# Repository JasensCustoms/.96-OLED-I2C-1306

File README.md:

# .96-OLED-I2C-1306
JasensCustoms.com version of an I2C OLED Screen.

These are provided for personal use only under the CC BY-NC 4.0 (https://creativecommons.org/licenses/by-nc/4.0/). This is a place that basic PCB outlines, cable pinouts, etc. will reside. You are free to update and fix errors, provide more context, and cotnribute to the repo.

Mechanical Drawing:

As you can see, placement is very specific and accurate. Standard PCB thickness, 1.6mm.

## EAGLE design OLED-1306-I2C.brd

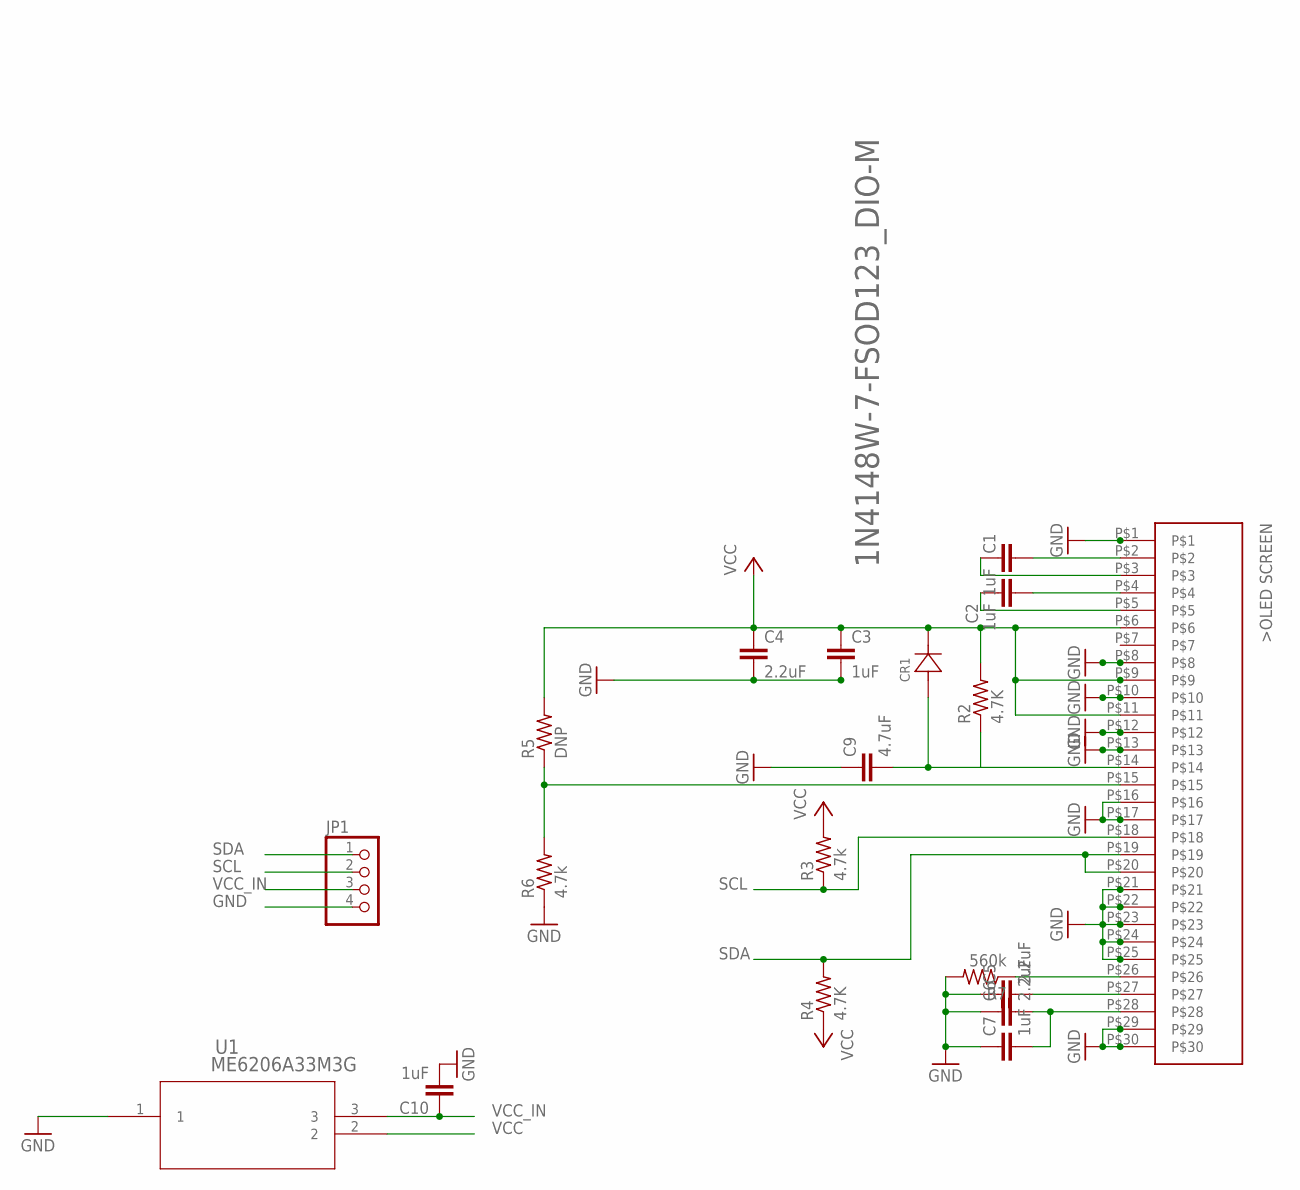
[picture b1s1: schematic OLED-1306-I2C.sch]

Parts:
C1, C2, C3, C7, C10: 1uF; C0603K
C4, C5, C6: 2.2uF; C0603K
C9: 4.7uF; C0603K
CR1: 1N4148W-7-FSOD123_DIO-M; SOD123_DIO-M
JP1: PINHD-1X4; 1X04
R2, R4: 4.7K; R0603
R3, R6: 4.7k; R0603
R5: DNP; R0603
R7: 560k; R0603
U1: ME6206A33M3G; IC_ME6206A33M3G_MNM
U$1: OLED1306-RIBON; OLED-1306-RIBBON

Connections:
GND: C3.2, C4.2, C5.1, C6.1, C7.1, C9.1, C10.2, JP1.4, R6.1, R7.2, U1.1, U$1.P$1, U$1.P$8, U$1.P$10, U$1.P$12, U$1.P$13, U$1.P$16, U$1.P$17, U$1.P$21, U$1.P$22, U$1.P$23, U$1.P$24, U$1.P$25, U$1.P$29, U$1.P$30
unnamed: C1.1, U$1.P$2
unnamed: C2.1, U$1.P$4
unnamed: C1.2, U$1.P$3
unnamed: C2.2, U$1.P$5
unnamed: C9.2, CR1.2, R2.1, U$1.P$14
unnamed: R5.1, R6.2, U$1.P$15
unnamed: R7.1, U$1.P$26
unnamed: C5.2, U$1.P$27
unnamed: C6.2, C7.2, U$1.P$28
SCL: JP1.2, R3.1, U$1.P$18
SDA: JP1.1, R4.2, U$1.P$19, U$1.P$20
VCC: C3.1, C4.1, CR1.1, R2.2, R3.2, R4.1, R5.2, U1.2, U$1.P$6, U$1.P$9, U$1.P$11
VCC_IN: C10.1, JP1.3, U1.3

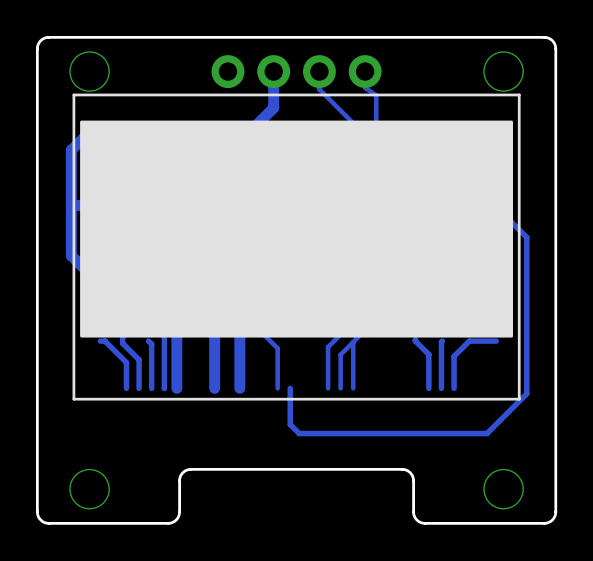
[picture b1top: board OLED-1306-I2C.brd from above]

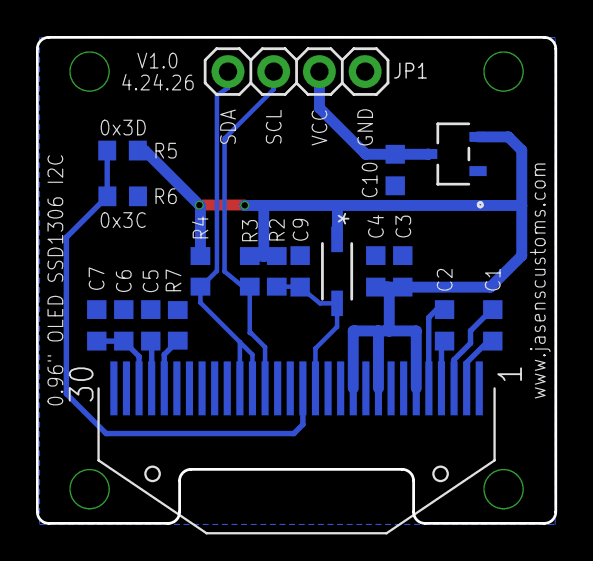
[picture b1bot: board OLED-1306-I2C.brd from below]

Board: 2 copper layers, 28.8 x 27.0 mm, 19 parts (19 on the bottom side), 14 nets.

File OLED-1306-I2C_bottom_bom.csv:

Comment,Designator,Footprint,LCSC Part #,QTY,Price,Total Price
1N4148W-7-FSOD123_DIO-M,CR1,SOD123_DIO-M,C917030,1,0.0057,0.0057
1uF,C1 C2 C3 C7 C10,C0603K,C15849,5,0.0078,0.039
2.2uF,C4 C5 C6,C0603K,C913904,3,0.0227,0.0681
4.7K,R2 R3 R4 R6,R0603,C99782,4,0.0014,0.0056
4.7uF,C9,C0603K,C307467,1,0.0295,0.0295
560k,R7,R0603,C137699,1,0.0017,0.0017
DNP,R5,R0603,DNP,1,,0
ME6206A33M3G,U1,IC_ME6206A33M3G_MNM,C35259,1,0.0526,0.0526
OLED1306-RIBBON-WHITE,U$1,OLED-1306-RIBBON,,1,,0
R/A PIN HEADER,J1,2.54mm PINHEAD,C42431821,1,0.022,0.022

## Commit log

2026-06-28 Update README with licensing and context
    Added licensing information and repository purpose.
2026-06-28 Add image to README for OLED project
    Added an image to the README for better visualization.
2026-06-28 Initial commit of EagleCAD files, BOM, and CSV.
    Part upload.

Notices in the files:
parts and their libraries:
COPYRIGHT: Copyright (C) 2026 Ultra Librarian. All rights reserved.
